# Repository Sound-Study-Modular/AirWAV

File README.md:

# Sound Study Modular AirWAV

##Information for re-use, adaptations or derivative works

Sound Study Modular is trademarked, and should not be used on any of works you create from these files.

We ask that if you want to re-use all or part of the files provided on github that you change the name of the product to something else

##What is this module?

The Sound Study Modular Air Wav is a virtual radio module, so it behaves a bit like a radio. It is designed to be a source of unexpected audio, not a drum loop player or a sample mangler.

Like a radio, this module works on a series of banks and stations. Each of the 16 banks can contain many different stations. Each station is .raw audio file stored in a bank directory on the SD card. Choose a bank by pressing and holding the RESET switch. Choose a station by turning the STATION knob or plugging a voltage into TUNE.
Detailed controls and displays
Adding samples to the SD Card

Full instructions and tools are in the <a href="http://www.soundstudymodular.com/assembly-instructions/air-wav-assembly-instructions/#sdCard">Setting up the SD Card</a> Section.

##Bank and meter LEDs

The LEDs at the top do two jobs. When audio is playing, they act as a simple VU meter. While choosing banks, they show the bank number in binary

- 0 ○○○○

- 1 ●○○○

- 2 ○●○○

- 3 ●●○○

- 4 ○○●○

- 5 ●○●○

- 6 ○●●○

- 7 ●●●○

- 8 ○○○●

- 9 ●○○●

- 10 ○●○●

- 11 ●●○●

- 12 ○○●●

- 13 ●○●●

- 14 ○●●●

- 15 ●●●●

##Station knob

This is how you choose which file to play from the current folder. It works exactly like a radio tuning knob.

You can put up to 75 files in each folder, but with that many files it might be hard to accurately tune to a station.
If you're between stations, you might get a rapid juddering sound as the module slips between stations. Just retune the knob. If you find it a big problem, put fewer files in each directory so the channels are more spaced out.
Like real radio stations, the files continue to play in the background - they don't re-trigger each time you select a new station.

##Start knob

This knob sets where the file will play from if you press the RESET button. It does nothing until you press the 'Reset' button! (This behaviour can be changed by editing settings.txt)

It's quite a coarse control, with a resolution of 512 steps. So, if you have a 30 minute radio show, the smallest shift you can make will be around 3.5 seconds. If you're playing a 4 second loop, the control will be finer.

##Reset button & LED

TAP the Reset button restarts the current track at the point determined by the Start knob or the Start CV input.

If you're playing a large file (a 30 minute .raw file is 150mb) it will take a few milliseconds to skip to the end of the file, so the button feels less responsive than it does with smaller files, or the earlier parts of bigger files.

HOLD the Reset button for more than 200ms to change banks. Keep the button held down to skip through all 16 banks.

Bank position is saved on the module after power-down.

##SD Card Slot

Full details of the SD file structure are here: <a href="http://www.soundstudymodular.com/assembly-instructions/air-wav-assembly-instructions/#sdCard">SD Card Details</a>

It's possible to hot-swap SD cards. If the module detects the SD card has been removed, it will reboot. When the module boots up, it looks for an SD card for a while - the bank LEDs flash when no card is present. After a while it will give up, and you'll need to turn the power on and off.

##Tune CV Input

This is the CV equivalent of the Station Pot. If the CV changes, the module will immediately re-tune to the relevant station.

The module 'understands' 0v to +5v signals, and is protected against higher or negative voltages.
The CV input is added to the knob position; if the knob is at 12 o'clock and 2.5v is applied to the CV, it's the equivalent of the knob being fully clockwise. Unfortunately you can't 'pull the pot down' by applying a negative voltage.

##Start CV input

This is the CV equivalent of the Start pot. Like the start pot, it does nothing until a 'Reset' CV is received. This CV input behaves like the Tune CV - it's zero to +5v, added to the pot position.
Reset Trigger input

A positive clock here triggers the reset button. It should not trigger the bank change.
##Output

This is a normal modular-level audio output.

The output level is set by the trimmer on the back of the module

The output is AC-coupled so cannot output control voltages

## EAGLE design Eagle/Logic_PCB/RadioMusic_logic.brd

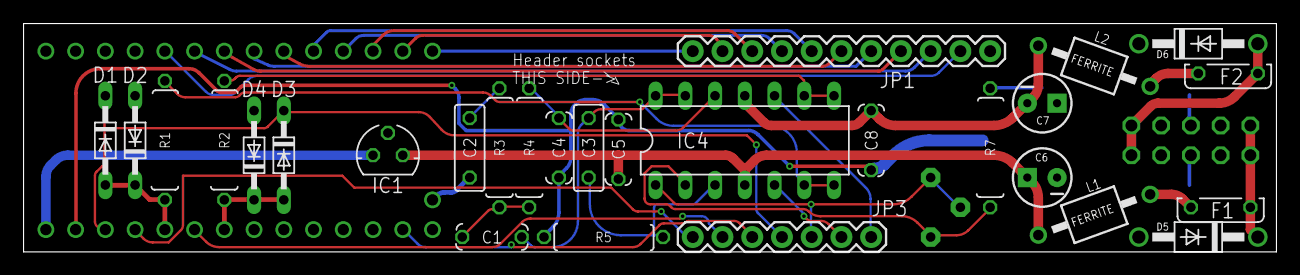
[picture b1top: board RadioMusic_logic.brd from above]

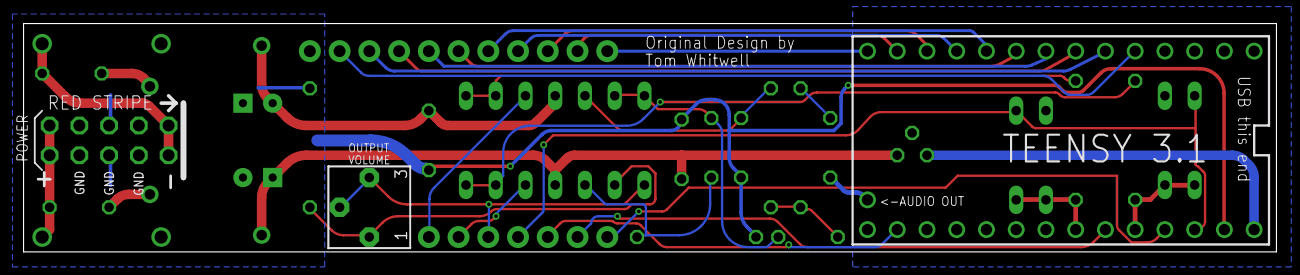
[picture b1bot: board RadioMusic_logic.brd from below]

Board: 4 copper layers, 107.0 x 19.5 mm, 31 parts (3 on the bottom side), 37 nets.

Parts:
C1, C4: 1n; C050-024X044
C2, C3: 100n; C050-025X075
C5, C8: 100n; C050-024X044
C6, C7: 10uf; CPOL-RADIAL-10UF-25V
D1, D2, D3, D4: BAT42; DO34-7
D5, D6: 1N4001; DO41-10
F1, F2: FUSE; C050H075X075
IC1: 78LXX
IC4: TL074; DIL14
JP1: M11PTH; 1X11
JP3: 1X07
L1, L2: BL01RN1A
OUTPUT: 50k; 3362P
R1, R2: 47R; 0207/10
R3, R4: 8.2k; 0207/10
R5: 330K; 0207/10
R7: 1k; 0207/10
SV1: MA05-2
U1: TEENSY_3.1_TW

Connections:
+3.3V: D1.C, D3.C, JP3.4, U1.3.3V
+5V: IC1.OUT, U1.VIN
+12V: C5.2, C6.1, IC1.IN, IC4.4, L1.1
+12V_INLET: D5.C, F1.1, SV1.9, SV1.10
-12V: C7.2, C8.2, IC4.11, L2.1
-12V_INLET: D6.A, F2.1, SV1.1, SV1.2
AUDIO_OUT: IC4.1, JP3.5, OUTPUT.2, OUTPUT.3
CHANNEL_CV: IC4.5, JP3.6
CHANNEL_POT: JP3.1, U1.23/A9
DAC: C2.1, U1.DAC
DGND: D2.A, D4.A, IC1.GND, U1.GND
GND: C4.2, C5.1, C6.2, C7.1, C8.1, D5.A, D6.C, JP1.1, R5.1, R7.2, SV1.3, SV1.4, SV1.5, SV1.6, SV1.7, SV1.8, U1.AGND
LED1: JP1.2, U1.3
LED2: JP1.3, U1.4
LED3: JP1.4, U1.5
LED4: JP1.5, U1.6
LED_RESET: JP1.10, U1.11
MISO: JP1.11, U1.12
MOSI: JP1.6, U1.7
unnamed: IC4.8, IC4.9, R2.2
unnamed: C4.1, IC4.12, R4.2
unnamed: IC4.6, IC4.7, R1.2
unnamed: C1.1, R3.1, R4.1
unnamed: C1.2, C3.1, IC4.13, IC4.14
unnamed: C3.2, IC4.3, R5.2
unnamed: IC4.2, OUTPUT.1, R7.1
unnamed: C2.2, R3.2
unnamed: F1.2, L1.2
unnamed: F2.2, L2.2
PIN20/A6: D3.A, D4.C, R2.1, U1.20/A6
PIN22/A8: D1.A, D2.C, R1.1, U1.22/A8
RESET_CV: JP1.8, U1.9
RESET_SW: JP1.7, U1.8
SCLK: JP3.3, U1.14/A0
SS: JP1.9, U1.10
TIME_CV: IC4.10, JP3.7
TIME_POT: JP3.2, U1.21/A7

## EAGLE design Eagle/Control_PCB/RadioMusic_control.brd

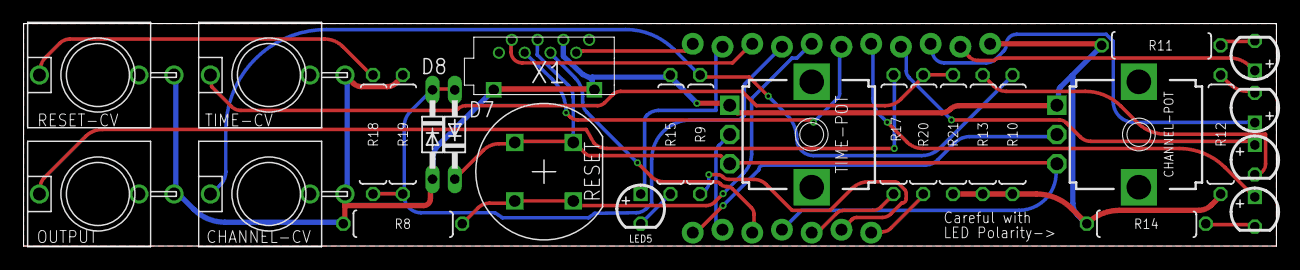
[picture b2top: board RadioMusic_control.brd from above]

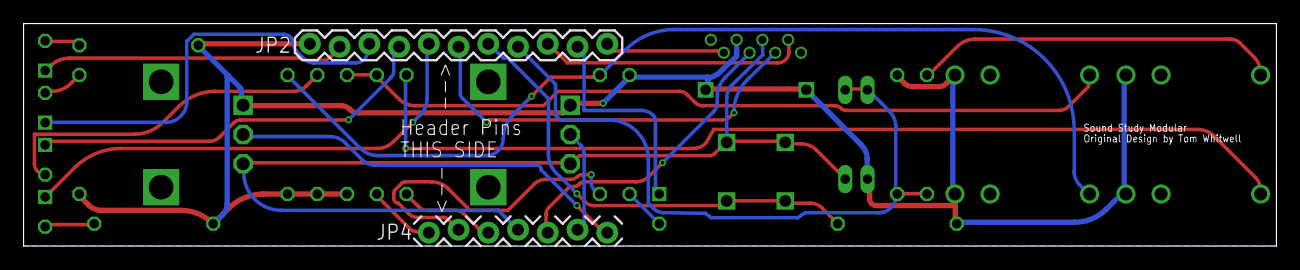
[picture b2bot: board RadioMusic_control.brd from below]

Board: 4 copper layers, 107.0 x 19.0 mm, 30 parts (2 on the bottom side), 27 nets.

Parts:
CHANNEL-CV: WQP-PJ301M-12_JACK
CHANNEL-POT: 50k; EVUF
D7, D8: BAT42; DO34-7
JP2: M11LOCK; 1X11_LOCK
JP4: 1X07_LOCK
LED1, LED2, LED3, LED4, LED5: LED3MM
OUTPUT: WQP-PJ301M-12_JACK
R8: 10k; 0207/10
R9, R20: 22k; 0207/10
R10, R21: 47k; 0207/10
R11, R12, R13, R14, R15: 1.5k; 0207/10
R17, R18: 220R; 0207/10
R19: 100k; 0207/10
RESET: D6_PUSH_SWITCH; D6_BUTTON_RND
RESET-CV: WQP-PJ301M-12_JACK
TIME-CV: WQP-PJ301M-12_JACK
TIME-POT: 50k; EVUF
X1: VERT_SD_CARD_REV2; VERT_MICROSD_REV2

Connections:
+3.3V_F: CHANNEL-POT.3, D7.C, JP4.4, RESET.P$3, RESET.P$4, TIME-POT.3, X1.P$4
AUDIO_OUT_F: JP4.5, R17.1
CHANNEL_CV_F: JP4.6, R9.1
CHANNEL_POT_F: CHANNEL-POT.2, JP4.1
GND_F: CHANNEL-CV.P$3, CHANNEL-POT.1, D8.A, JP2.1, OUTPUT.P$3, R8.1, R10.1, R11.1, R12.1, R13.1, R14.1, R15.2, R19.2, R21.1, RESET-CV.P$3, TIME-CV.P$3, TIME-POT.1, X1.GND1, X1.GND2, X1.P$6
LED1_F: JP2.2, LED1.A
LED2_F: JP2.3, LED2.A
LED3_F: JP2.4, LED3.A
LED4_F: JP2.5, LED4.A
LED_RESET_F: JP2.10, LED5.A
MISO_F: JP2.11, X1.P$7
MOSI_F: JP2.6, X1.P$3
unnamed: OUTPUT.P$1, R17.2
unnamed: CHANNEL-CV.P$1, R9.2, R10.2
unnamed: R18.2, RESET-CV.P$1
unnamed: LED1.K, R11.2
unnamed: LED2.K, R12.2
unnamed: LED3.K, R13.2
unnamed: LED4.K, R14.2
unnamed: LED5.K, R15.1
RESET_CV_F: D7.A, D8.C, JP2.8, R18.1, R19.1
RESET_SW_F: JP2.7, R8.2, RESET.P$1, RESET.P$2
SCLK_F: JP4.3, X1.P$5
SS_F: JP2.9, X1.P$2
TEMP: R20.2, R21.2, TIME-CV.P$1
TIME_CV_F: JP4.7, R20.1
TIME_POT_F: JP4.2, TIME-POT.2

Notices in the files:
parts and their libraries:
SparkFun-Connectors: Licensing: CC v3.0 Share-Alike You are welcome to use this library for commercial purposes.
